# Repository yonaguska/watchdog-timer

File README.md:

# watchdog-timer
A retriggerable monostable based on the ICM7555, useful in watchdog applications for microcontrollers. 

To use the watchdog;
1. Have your code generate a short negative RESET signal to the watchdog, to initialize the circuit.
 NOTE: there is a capacitor to GND that should initialize the watchdog at power-on.
2. The watchdog has a timeout of about 400 seconds, at which time it will drive the OUTPUT LOW. In addition to the OUPUT signal, a capacitivly-coupled PULSE will temporarily go LOW.
3. To keep the watchdog from timing out, generate a short LOW pulse to the /TRIGGER pin before the 400 seconds is up.

Testing the watchdog units:

1. A Raspberry Pi Pico based test system was developed that runs tests on each watchdog I sell. Besides being a hardware/software developer, I am a professional test engineer with over thirty years of automated system test development experience.
2. The testing checks to insure the timeout period is at least 400 seconds, any board timing out in less than 400 seconds is rejected. It also insures the retriggering works ten times consecutively and then times out properly.

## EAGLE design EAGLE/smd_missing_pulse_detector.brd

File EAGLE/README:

These are the pertinent Eagle files

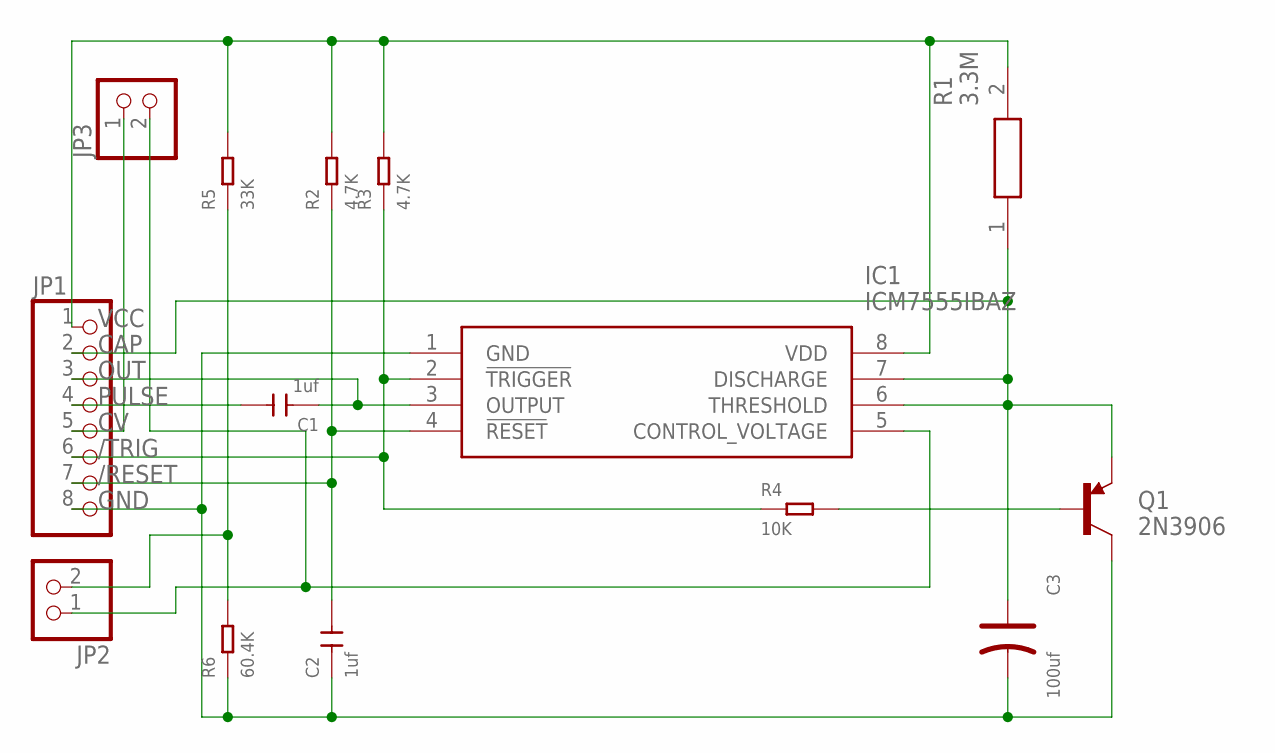
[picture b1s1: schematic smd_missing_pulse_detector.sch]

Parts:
C1, C2: 1uf; C0805
C3: 100uf; AVX-B
IC1: ICM7555IBAZ; SOIC127P600X175-8N
JP1: PINHD-1X8; 1X08
JP2, JP3: PINHD-1X2; 1X02
Q1: 2N3906; SOT23-3
R1: 3.3M; RESC1608X50N
R2, R3: 4.7K; R0603
R4: 10K; R0603
R5: 33K; R0603
R6: 60.4K; R0603

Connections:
/RESET: C2.2, IC1.4 (!RESET), JP1.7, R2.1
/TRIG: IC1.2 (!TRIGGER), JP1.6, R3.1, R4.1
CAP: C3.+, IC1.6 (THRESHOLD), IC1.7 (DISCHARGE), JP1.2, Q1.2 (E), R1.1
CV: IC1.5 (CONTROL_VOLTAGE), JP2.1, JP3.2
GND: C2.1, C3.-, IC1.1 (GND), JP1.8, Q1.3 (C), R6.1
unnamed: Q1.1 (B), R4.2
unnamed: JP2.2, R5.1, R6.2
unnamed: JP1.5, JP3.1
OUT: C1.1, IC1.3 (OUTPUT), JP1.3
PULSE: C1.2, JP1.4
VCC: IC1.8 (VDD), JP1.1, R1.2, R2.2, R3.2, R5.2

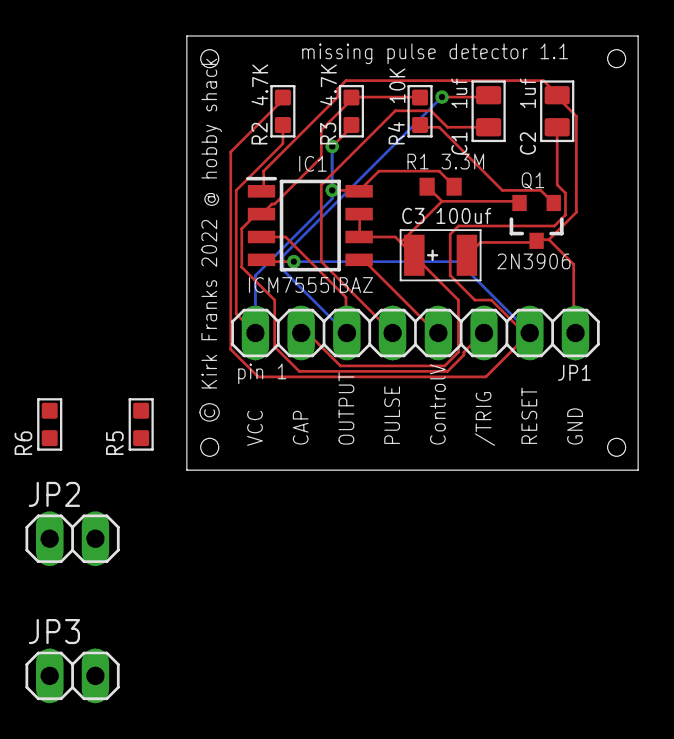
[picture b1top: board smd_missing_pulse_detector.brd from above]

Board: 2 copper layers, 25.1 x 24.1 mm, 14 parts (0 on the bottom side), 11 nets.

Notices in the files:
EAGLE/smd_missing_pulse_detector.brd:
© Kirk Franks 2022 @ hobby shack
parts and their libraries:
User-Submitted: Licensing: Creative Commons ShareAlike 4.0 International - https://creativecommons.org/licenses/by-sa/4.0
